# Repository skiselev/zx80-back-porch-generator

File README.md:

# zx80-back-porch-generator
 Back Porch Video Signal Generator for ZX80

## Description

This circuit modifies the Sinclair ZX80 video output signal and adds the "back porch" part of the synchronization pulse of the video signal, so that it can be used with modern TVs.

The circuit is build on a PCB that can be installed instead of the video modulator circuit.

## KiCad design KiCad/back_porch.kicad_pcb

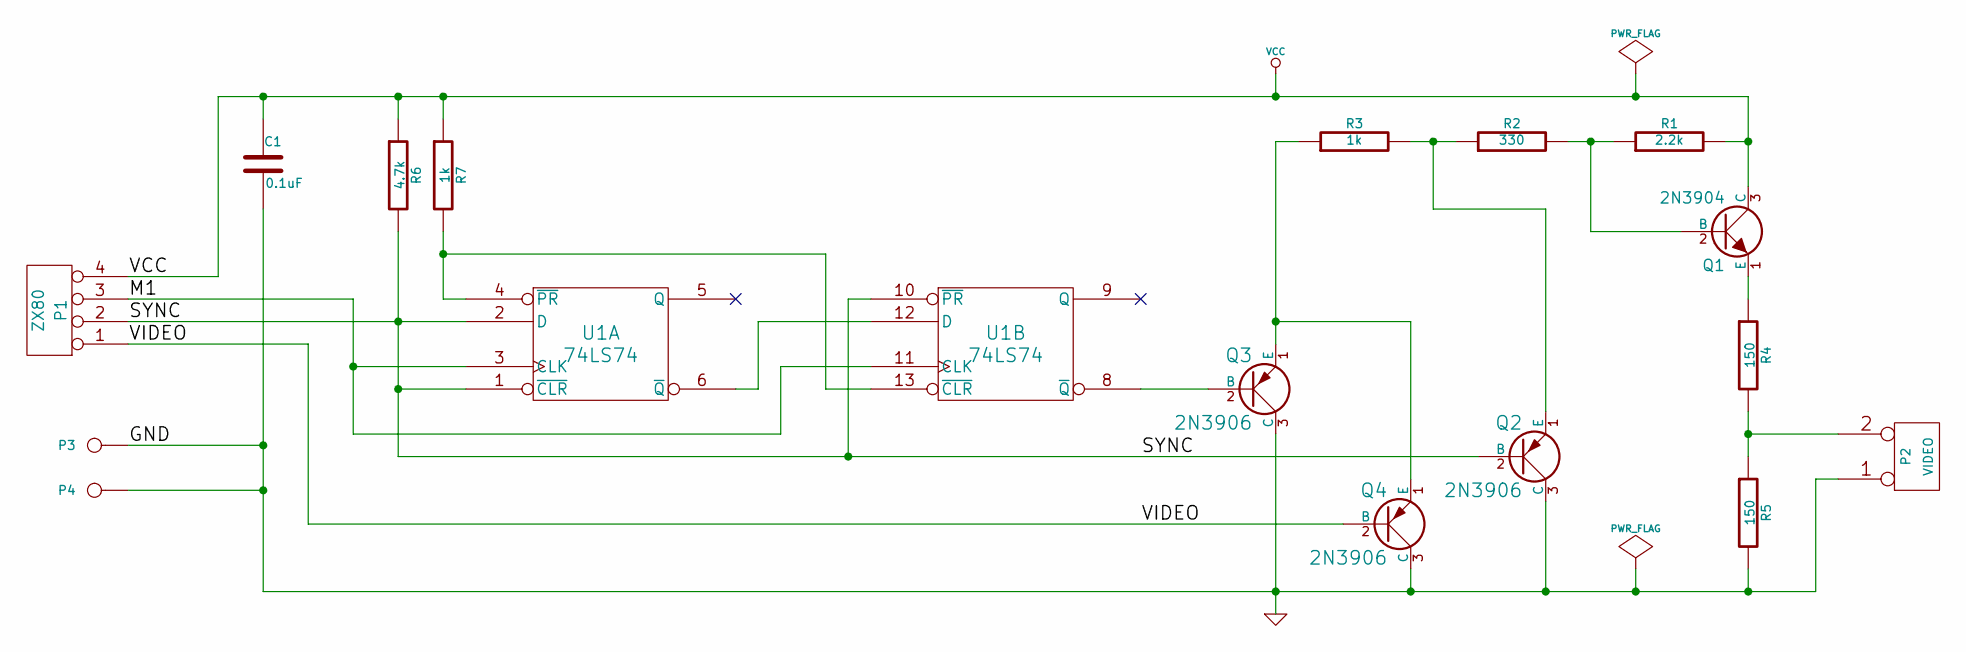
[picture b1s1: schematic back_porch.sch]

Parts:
C1: 0.1uF
P1: ZX80
P2: VIDEO
P3, P4: CONN_1
Q1: 2N3904
Q2, Q3, Q4: 2N3906
R1: 2.2k
R2: 330
R3, R7: 1k
R4, R5: 150
R6: 4.7k
U1: 74LS74

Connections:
/M1: P1.3, U1.3 (CLK), U1.11 (CLK)
/SYNC: P1.2, Q2.2 (B), R6.2, U1.1 (~CLR), U1.2 (D), U1.10 (~PR)
/VIDEO: P1.1, Q4.2 (B)
GND: C1.2, P2.1, P3.1, P4.1, Q2.3 (C), Q3.3 (C), Q4.3 (C), R5.2, U1.7 (GND)
unnamed: Q2.1 (E), R2.1, R3.2
unnamed: R7.2, U1.4 (~PR), U1.13 (~CLR)
unnamed: Q1.2 (B), R1.1, R2.2
unnamed: Q1.1 (E), R4.1
unnamed: P2.2 (PM), R4.2, R5.1
unnamed: U1.6 (~Q), U1.12 (D)
unnamed: Q3.2 (B), U1.8 (~Q)
unnamed: Q3.1 (E), Q4.1 (E), R3.1
VCC: C1.1, P1.4, Q1.3 (C), R1.2, R6.1, R7.1, U1.14 (VCC)

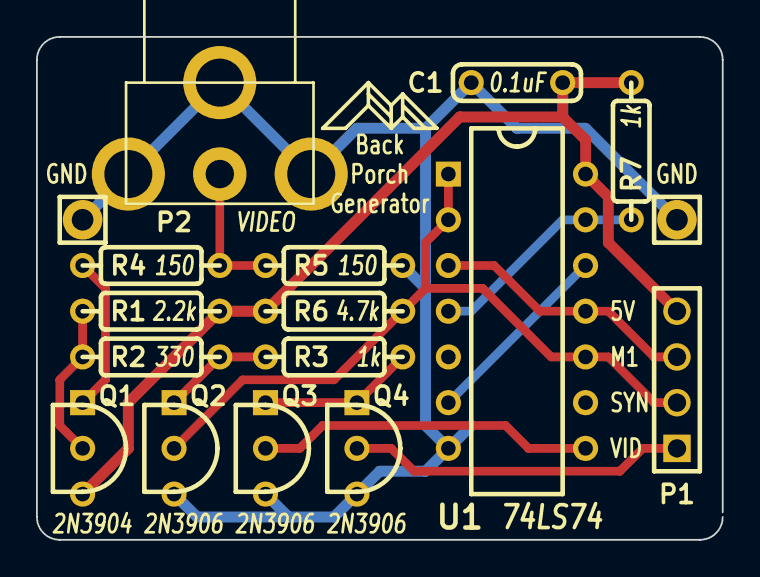
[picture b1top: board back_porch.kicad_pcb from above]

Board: 2 copper layers, 38.1 x 27.9 mm, 17 parts (0 on the bottom side), 13 nets.

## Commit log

2025-10-17 Add KiCad and Gerber files
2025-10-17 Add ZX80 PCB photo with the back porch generator
